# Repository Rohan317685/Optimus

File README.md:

# Optimus 

This is a LED blinky sort of, it uses a capacitor for a hearbeat like effect where it dim's down after removing your finger from the two pin's.

I made this because it was unique and I was really curious on how electricty travelled through the human body.

I'm using a extra pair of 2 pin's where you basically keep your finger ontop of the 2 pin's and essentially your finger act's as a resistor and trigger's the darlington pair transistors which let current through so it can light up the lighbulbs!

---

## Simulation

It work's using a Darlington pair which essentially amplifies the signal to the transistor's so when you keep your finger which is represented by the 10m resistor the current travel's through and trigger's the darlington pair 
which then make's the current flow through to the led's, when you take your finger of the capacitor releases excess energy which then create's a sort of dimming effect for a couple of second's!

.gif)

[Link to Demo](https://falstad.com/circuit/circuitjs.html?ctz=DwYwlgTgBAZgvAIgIwKgFwM6IAwDpsEECsqYIiAzABwBMuA7AGw1G1IAsFAnF9o+6hAAjREWyoADiIRjUANwijUAW0yiApgFokKAHwAoKFGBooAD0RUujKO3ZUoXGg7tVU8BOKgSAdohRQQur+BCoA9ogAJuowAIYArgA2aPJBiJp4ROzY9khEFFkU7FxUVIyp5J64jEQlREiMeVzs9EhcRDQIAPQGRibmiPQdUAU0UPRU7CMd7jiSfsioacihUMoRCNFxSSlQcsvauEilk1QU2GVlFPR2Wm57QpWZ2bkdBew12EQkPYbGIAMEIx6GNRlBgWNOJ1YIgBFBKkh8IRkSiCEgtPRSHIcEiAhhFJ55JFLLgeGSeKUdHkkJjfn0AOaAiG2ChjZkfOEecR04wAd0BQ1Bw2Zo1mhJ5wH5FiBIOmbIucrF3N6xmg0sYCrBHQcophhKgBLw2BQEqlomcUAa2EcFqtSu6KuAACVAU4HFabe6kNCuaheb61rEzNiEFwHX9JQLJiMKDYJlMaNl7aaownsp6oImvL6U9K3ZaNRms8nHWbQxasxmoSWI2X4yNGA5664a3069HXFArDYW3rlbXXRaOZactaOa3VYOXPwM7UfXMDSFQhK1SF08OkKOoHP7YuVsvHQAZACiABEp9unBmauU9dD1lEYglkppEupIoICQEQPSF8IF8ojw4sa4Z9Ce57Spu6ZziO6Y3mK94bFsz5oK+76fv4gi-vq-76oBTz4CajqMnmFo3hm9A5BOwAkWu1rkVB1qUZycy5uaOrDNqBbZqxjphFA6gLMcqAYBIiD8GKZgUJIcwqn0Eh7AuGCVD8cnGApIbSVAynAXwLCgcYXRhAYwBdOAEAGEAA)

---
## Schematic

## PCB

---

Thank's @shadow and @cookie with coffee for helping me in the huddle! Also thx @rudy for the amazing guide!

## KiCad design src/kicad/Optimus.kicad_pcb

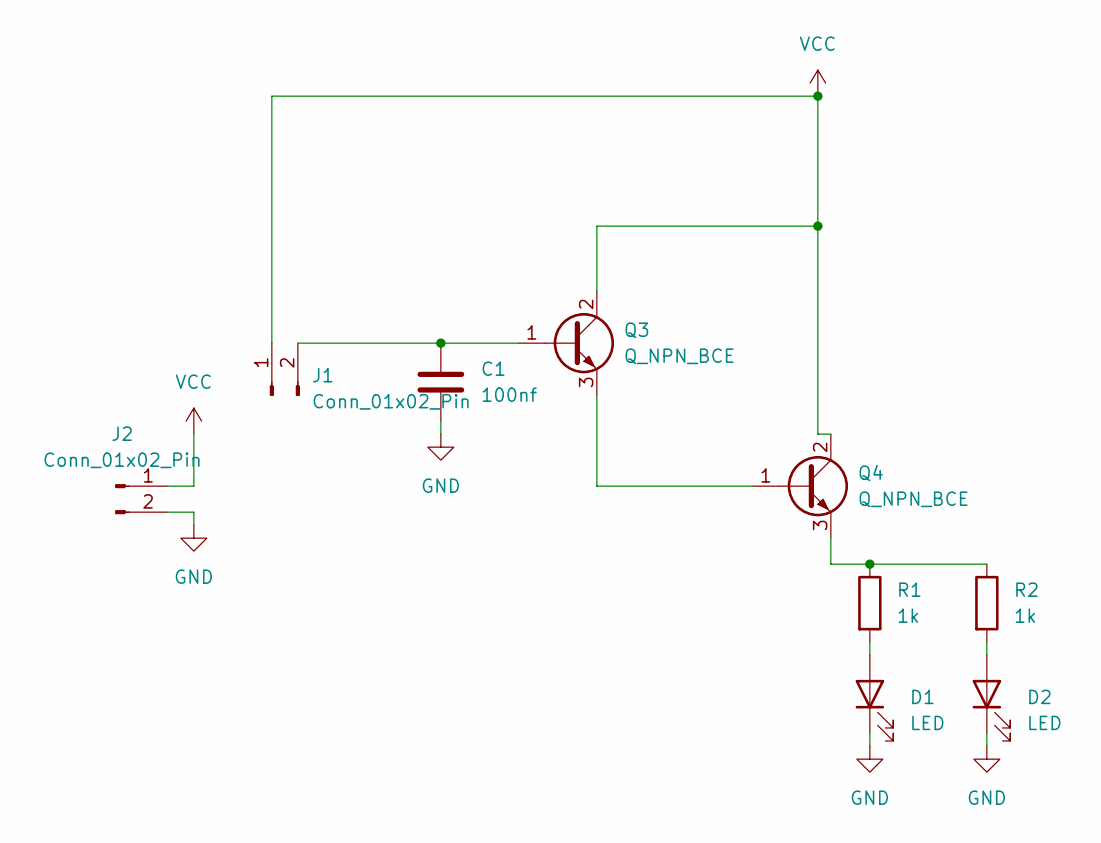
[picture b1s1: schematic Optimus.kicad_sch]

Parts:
C1: 100nf; C_Disc_D5.0mm_W2.5mm_P5.00mm
D1, D2: LED; LED_D5.0mm
J1, J2: Conn_01x02_Pin; PinHeader_1x02_P2.54mm_Vertical
Q3, Q4: Q_NPN_BCE; TO-92L_Inline_Wide
R1, R2: 1k; R_Axial_DIN0204_L3.6mm_D1.6mm_P7.62mm_Horizontal

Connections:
GND: C1.2, D1.1 (K), D2.1 (K), J2.2
unnamed: D1.2 (A), R1.2
unnamed: D2.2 (A), R2.2
unnamed: C1.1, J1.2, Q3.1 (B)
unnamed: Q3.3 (E), Q4.1 (B)
unnamed: Q4.3 (E), R1.1, R2.1
VCC: J1.1, J2.1, Q3.2 (C), Q4.2 (C)

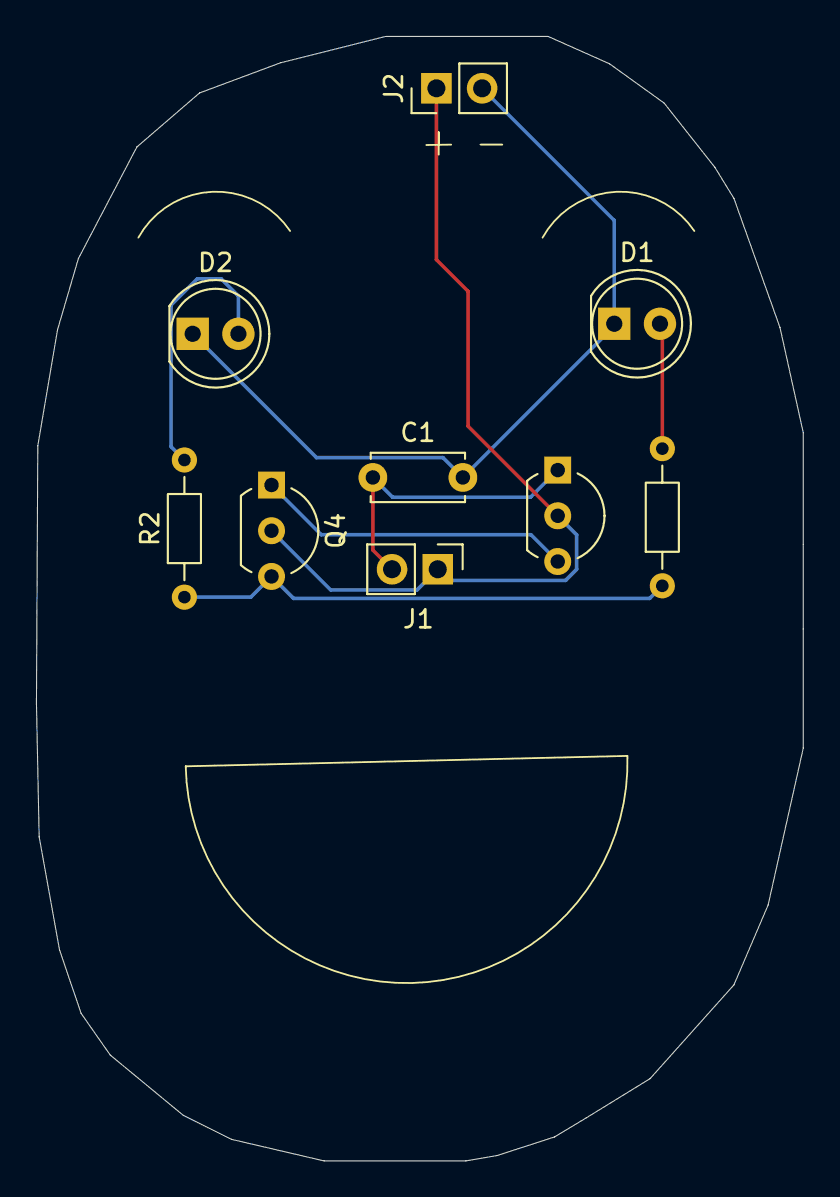
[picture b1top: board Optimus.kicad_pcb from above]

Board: 2 copper layers, 42.6 x 62.5 mm, 9 parts (0 on the bottom side), 7 nets.
